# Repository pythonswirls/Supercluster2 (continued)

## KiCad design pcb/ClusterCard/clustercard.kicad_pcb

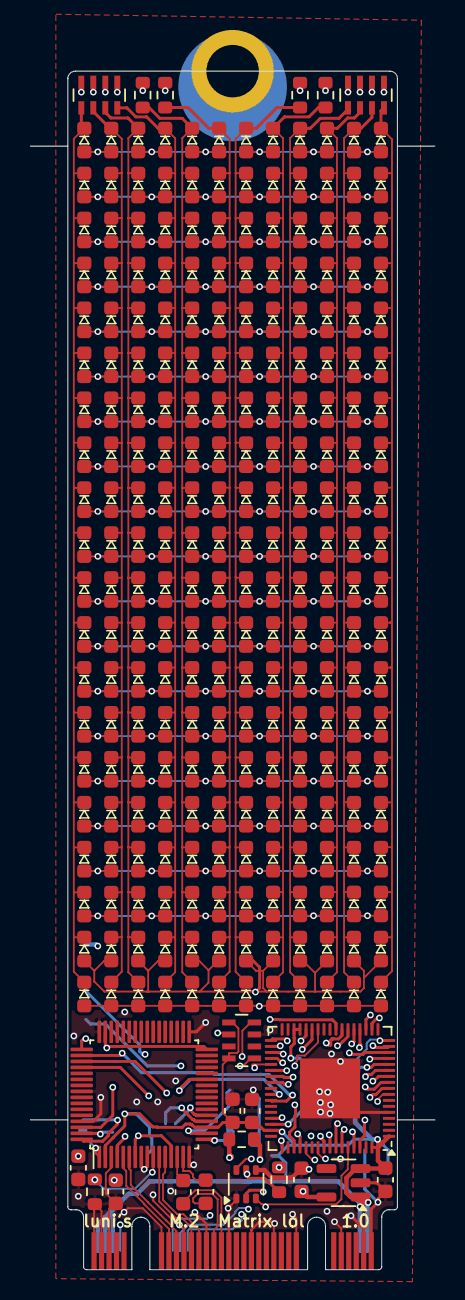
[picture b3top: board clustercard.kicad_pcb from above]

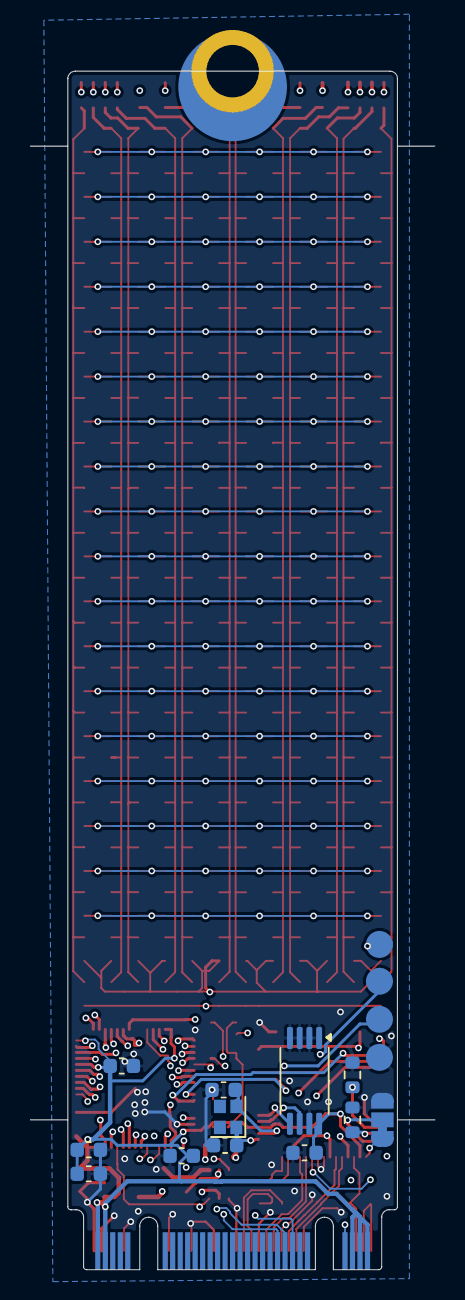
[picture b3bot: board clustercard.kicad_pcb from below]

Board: 4 copper layers, 27.0 x 80.0 mm, 276 parts (13 on the bottom side), 77 nets.

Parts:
C1, C2, C3, C10, C12, C15, C21, C22, C23, C24, C25: 100n; C_0603_1608Metric
C8, C11: 10u; C_0603_1608Metric
C16, C17: 27p; C_0603_1608Metric
D121, D122, D123, D124, D125, D126, D127, D128, D129, D130, D131, D132, D133, D134, D135, D136, D137, D138, D139, D140, D141, D142, D143, D144, D145, D146, D147, D148, D149, D150, D151, D152, D153, D154, D155, D156, D157, D158, D159, D160, D161, D162, D163, D164, D165, D166, D167, D168, D169, D170, D171, D172, D173, D174, D175, D176, D177, D178, D179, D180, D181, D182, D183, D184, D185, D186, D187, D188, D189, D190, D191, D192, D193, D194, D195, D196, D197, D198, D199, D200, D201, D202, D203, D204, D205, D206, D207, D208, D209, D210, D211, D212, D213, D214, D215, D216, D217, D218, D219, D220, D221, D222, D223, D224, D225, D226, D227, D228, D229, D230, D231, D232, D233, D234, D235, D236, D237, D238, D239, D240, D241, D242, D243, D244, D245, D246, D247, D248, D249, D250, D251, D252, D253, D254, D255, D256, D257, D258, D259, D260, D261, D262, D263, D264, D265, D266, D267, D268, D269, D270, D271, D272, D273, D274, D275, D276, D277, D278, D279, D280, D281, D282, D283, D284, D285, D286, D287, D288, D289, D290, D291, D292, D293, D294, D295, D296, D297, D298, D299, D300, D301, D302, D303, D304, D305, D306, D307, D308, D309, D310, D311, D312, D313, D314, D315, D316, D317, D318, D319, D320, D321, D322, D323, D324, D325, D326, D327, D328, D329, D330, D331, D332, D333, D334, D335, D336, D337, D338, D339, D340, D341, D342, D343, D344, D345, D346, D347, D348, D349, D350, D351, D352, D353, D354, D355, D356, D357, D358, D359, D360: LEDdiag0603; LED_0603
JP2: Jumper_3_Bridged12; SolderJumper-3_P1.3mm_Bridged12_RoundedPad1.0x1.5mm
Q1: UMH3N; SOT-363_SC-70-6
R8, R13, R14, R15, R16: 1k; R_0603_1608Metric
R9, R10, R11: 0; R_0603_1608Metric
R12: 12k; R_0603_1608Metric
RN5, RN6: 1k; R_Array_Concave_4x0603
RN8: 10k; R_Array_Concave_4x0603
TP1: TestPoint; Testpoint4
U1: CH382; LQFP-64_7x7mm_P0.4mm
U2: M.2-B+M-KEY-PCIe; M.2-B+M-KEY 2280
U4: M24C02-FDW; TSSOP-8_4.4x3mm_P0.65mm
U5: QFN-68-1EP_8x8mm_P0.4mm_EP4x4mm
U6: AP2112K-1.8; SOT-23-5
Y1: 22.1184MHz; Crystal_SMD_2016-4Pin_2.0x1.6mm

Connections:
1V8: C10.2, C11.2, R9.1, U1.4 (VCC18), U1.32 (VCC18), U1.47 (VCC18), U6.5 (VOUT)
1V8A: C12.2, R9.2, U1.7 (VCC18A), U1.13 (VCC18A)
/BOOT1: R8.2, U5.28 (PB2/BOOT1)
/CKSEL: JP2.2 (C), U1.64 (CKSEL)
/CLKREQ#: RN8.2 (R2.1), U2.P$52 (CLKREQ#)
/CLK_32k: U2.P$68 (SUSCLK(32kHz)), U5.58 (PB3)
/DTR: Q1.2 (B1), U1.52 (DTR0)
/PECK+: U1.5 (PECK+), U2.P$55 (REFCLK+)
/PECK-: U1.6 (PECK-), U2.P$53 (REFCLK-)
/PER+: U1.11 (PER+), U2.P$49 (PER0+)
/PER-: U1.12 (PER-), U2.P$47 (PER0-)
/PET+: C2.2, U1.15 (PET+)
/PET-: C1.2, U1.14 (PET-)
/RST#: JP2.1 (A), U1.1 (PERST#), U2.P$50 (PERST#)
/RST_CH32#: Q1.6 (C1), RN8.8 (R1.2), U5.8 (NRST)
/RTS: Q1.5 (B2), R8.1, U1.51 (RTS0)
/RX: U1.27 (RXD0), U5.44 (PA9)
/TX: U1.50 (TXD0), U5.45 (PA10)
/WAKE#: U2.P$54 (PEWAKE#), U5.56 (PC12)
BOOT0: Q1.3 (C2), RN8.5 (R4.2), U5.63 (BOOT0)
GND: C3.1, C8.1, C10.1, C11.1, C12.1, C15.1, C16.2, C17.2, C21.2, C22.2, C23.2, C24.2, C25.2, JP2.3 (B), Q1.1 (E1), Q1.4 (E2), R10.2, R11.2, R12.2, RN8.7 (R2.2), TP1.1, U1.3 (GND), U1.8 (GND), U1.9 (GND), U1.16 (GND), U1.33 (GND), U1.48 (GND), U1.56 (GND), U1.61 (GND), U2.P$1 (CONFIG3/GND), U2.P$3 (GND), U2.P$9 (GND), U2.P$21 (CONFIG_0/GND), U2.P$27 (GND), U2.P$33 (GND), U2.P$39 (GND), U2.P$45 (GND), U2.P$51 (GND), U2.P$57 (GND), U2.P$71 (GND), U2.P$73 (GND), U2.P$75 (CONFIG_2/GND), U4.1 (E0), U4.2 (E1), U4.3 (E2), U4.4 (VSS), U4.7 (~WC), U5.5 (VSSA), U5.49 (VSS_2), U5.69 (VSS), U6.2 (GND)
unnamed: D121.1 (K), D133.1 (K), D145.1 (K), D157.1 (K), D169.1 (K), D181.1 (K), D193.1 (K), D205.1 (K), D217.1 (K), D229.1 (K), D241.1 (K), D253.1 (K), D265.1 (K), D277.1 (K), D289.1 (K), D301.1 (K), D313.1 (K), D325.1 (K), D337.1 (K), D349.1 (K), RN5.4 (R4.1)
unnamed: D122.1 (K), D134.1 (K), D146.1 (K), D158.1 (K), D170.1 (K), D182.1 (K), D194.1 (K), D206.1 (K), D218.1 (K), D230.1 (K), D242.1 (K), D254.1 (K), D266.1 (K), D278.1 (K), D290.1 (K), D302.1 (K), D314.1 (K), D326.1 (K), D338.1 (K), D350.1 (K), RN5.3 (R3.1)
unnamed: D123.1 (K), D135.1 (K), D147.1 (K), D159.1 (K), D171.1 (K), D183.1 (K), D195.1 (K), D207.1 (K), D219.1 (K), D231.1 (K), D243.1 (K), D255.1 (K), D267.1 (K), D279.1 (K), D291.1 (K), D303.1 (K), D315.1 (K), D327.1 (K), D339.1 (K), D351.1 (K), RN5.2 (R2.1)
unnamed: D124.1 (K), D136.1 (K), D148.1 (K), D160.1 (K), D172.1 (K), D184.1 (K), D196.1 (K), D208.1 (K), D220.1 (K), D232.1 (K), D244.1 (K), D256.1 (K), D268.1 (K), D280.1 (K), D292.1 (K), D304.1 (K), D316.1 (K), D328.1 (K), D340.1 (K), D352.1 (K), RN5.1 (R1.1)
unnamed: D125.1 (K), D137.1 (K), D149.1 (K), D161.1 (K), D173.1 (K), D185.1 (K), D197.1 (K), D209.1 (K), D221.1 (K), D233.1 (K), D245.1 (K), D257.1 (K), D269.1 (K), D281.1 (K), D293.1 (K), D305.1 (K), D317.1 (K), D329.1 (K), D341.1 (K), D353.1 (K), R13.1
unnamed: D126.1 (K), D138.1 (K), D150.1 (K), D162.1 (K), D174.1 (K), D186.1 (K), D198.1 (K), D210.1 (K), D222.1 (K), D234.1 (K), D246.1 (K), D258.1 (K), D270.1 (K), D282.1 (K), D294.1 (K), D306.1 (K), D318.1 (K), D330.1 (K), D342.1 (K), D354.1 (K), R14.1
unnamed: D127.1 (K), D139.1 (K), D151.1 (K), D163.1 (K), D175.1 (K), D187.1 (K), D199.1 (K), D211.1 (K), D223.1 (K), D235.1 (K), D247.1 (K), D259.1 (K), D271.1 (K), D283.1 (K), D295.1 (K), D307.1 (K), D319.1 (K), D331.1 (K), D343.1 (K), D355.1 (K), R15.1
unnamed: D128.1 (K), D140.1 (K), D152.1 (K), D164.1 (K), D176.1 (K), D188.1 (K), D200.1 (K), D212.1 (K), D224.1 (K), D236.1 (K), D248.1 (K), D260.1 (K), D272.1 (K), D284.1 (K), D296.1 (K), D308.1 (K), D320.1 (K), D332.1 (K), D344.1 (K), D356.1 (K), R16.1
unnamed: D129.1 (K), D141.1 (K), D153.1 (K), D165.1 (K), D177.1 (K), D189.1 (K), D201.1 (K), D213.1 (K), D225.1 (K), D237.1 (K), D249.1 (K), D261.1 (K), D273.1 (K), D285.1 (K), D297.1 (K), D309.1 (K), D321.1 (K), D333.1 (K), D345.1 (K), D357.1 (K), RN6.4 (R4.1)
unnamed: D130.1 (K), D142.1 (K), D154.1 (K), D166.1 (K), D178.1 (K), D190.1 (K), D202.1 (K), D214.1 (K), D226.1 (K), D238.1 (K), D250.1 (K), D262.1 (K), D274.1 (K), D286.1 (K), D298.1 (K), D310.1 (K), D322.1 (K), D334.1 (K), D346.1 (K), D358.1 (K), RN6.3 (R3.1)
unnamed: D131.1 (K), D143.1 (K), D155.1 (K), D167.1 (K), D179.1 (K), D191.1 (K), D203.1 (K), D215.1 (K), D227.1 (K), D239.1 (K), D251.1 (K), D263.1 (K), D275.1 (K), D287.1 (K), D299.1 (K), D311.1 (K), D323.1 (K), D335.1 (K), D347.1 (K), D359.1 (K), RN6.2 (R2.1)
unnamed: D132.1 (K), D144.1 (K), D156.1 (K), D168.1 (K), D180.1 (K), D192.1 (K), D204.1 (K), D216.1 (K), D228.1 (K), D240.1 (K), D252.1 (K), D264.1 (K), D276.1 (K), D288.1 (K), D300.1 (K), D312.1 (K), D324.1 (K), D336.1 (K), D348.1 (K), D360.1 (K), RN6.1 (R1.1)
unnamed: R11.1, U1.62 (MDPRT#)
unnamed: R10.1, U1.63 (MDSEL)
unnamed: R12.1, U1.10 (RREF)
unnamed: U1.20 (SCL), U4.6 (SCL)
unnamed: U1.21 (SDA), U4.5 (SDA)
unnamed: C16.1, U1.18 (XI), Y1.2
unnamed: C17.1, U1.17 (XO), Y1.1
unnamed: C2.1, U2.P$43 (PET0+)
unnamed: C1.1, U2.P$41 (PET0-)
PA0: D121.2 (A), D122.2 (A), D123.2 (A), D124.2 (A), D125.2 (A), D126.2 (A), D127.2 (A), D128.2 (A), D129.2 (A), D130.2 (A), D131.2 (A), D132.2 (A), U5.14 (PA0/WKUP/ADC0)
PA1: D133.2 (A), D134.2 (A), D135.2 (A), D136.2 (A), D137.2 (A), D138.2 (A), D139.2 (A), D140.2 (A), D141.2 (A), D142.2 (A), D143.2 (A), D144.2 (A), U5.15 (PA1/ADC1)
PA2: D145.2 (A), D146.2 (A), D147.2 (A), D148.2 (A), D149.2 (A), D150.2 (A), D151.2 (A), D152.2 (A), D153.2 (A), D154.2 (A), D155.2 (A), D156.2 (A), U5.16 (PA2/ADC2)
PA3: D157.2 (A), D158.2 (A), D159.2 (A), D160.2 (A), D161.2 (A), D162.2 (A), D163.2 (A), D164.2 (A), D165.2 (A), D166.2 (A), D167.2 (A), D168.2 (A), U5.19 (PA3/ADC3)
PA4: D169.2 (A), D170.2 (A), D171.2 (A), D172.2 (A), D173.2 (A), D174.2 (A), D175.2 (A), D176.2 (A), D177.2 (A), D178.2 (A), D179.2 (A), D180.2 (A), U5.20 (PA4/ADC4)
PA5: D181.2 (A), D182.2 (A), D183.2 (A), D184.2 (A), D185.2 (A), D186.2 (A), D187.2 (A), D188.2 (A), D189.2 (A), D190.2 (A), D191.2 (A), D192.2 (A), U5.21 (PA5/ADC5)
PA6: D193.2 (A), D194.2 (A), D195.2 (A), D196.2 (A), D197.2 (A), D198.2 (A), D199.2 (A), D200.2 (A), D201.2 (A), D202.2 (A), D203.2 (A), D204.2 (A), U5.22 (PA6/ADC6)
PA7: D205.2 (A), D206.2 (A), D207.2 (A), D208.2 (A), D209.2 (A), D210.2 (A), D211.2 (A), D212.2 (A), D213.2 (A), D214.2 (A), D215.2 (A), D216.2 (A), U5.23 (PA7/ADC7)
PB4: D217.2 (A), D218.2 (A), D219.2 (A), D220.2 (A), D221.2 (A), D222.2 (A), D223.2 (A), D224.2 (A), D225.2 (A), D226.2 (A), D227.2 (A), D228.2 (A), U5.59 (PB4)
PB5: D229.2 (A), D230.2 (A), D231.2 (A), D232.2 (A), D233.2 (A), D234.2 (A), D235.2 (A), D236.2 (A), D237.2 (A), D238.2 (A), D239.2 (A), D240.2 (A), U5.60 (PB5)
PB6: D241.2 (A), D242.2 (A), D243.2 (A), D244.2 (A), D245.2 (A), D246.2 (A), D247.2 (A), D248.2 (A), D249.2 (A), D250.2 (A), D251.2 (A), D252.2 (A), U5.61 (PB6/USB2DM)
PB7: D253.2 (A), D254.2 (A), D255.2 (A), D256.2 (A), D257.2 (A), D258.2 (A), D259.2 (A), D260.2 (A), D261.2 (A), D262.2 (A), D263.2 (A), D264.2 (A), U5.62 (PB7/USB2DP)
PB8: D265.2 (A), D266.2 (A), D267.2 (A), D268.2 (A), D269.2 (A), D270.2 (A), D271.2 (A), D272.2 (A), D273.2 (A), D274.2 (A), D275.2 (A), D276.2 (A), U5.64 (PB8)
PB9: D277.2 (A), D278.2 (A), D279.2 (A), D280.2 (A), D281.2 (A), D282.2 (A), D283.2 (A), D284.2 (A), D285.2 (A), D286.2 (A), D287.2 (A), D288.2 (A), U5.65 (PB9)
PB10: D289.2 (A), D290.2 (A), D291.2 (A), D292.2 (A), D293.2 (A), D294.2 (A), D295.2 (A), D296.2 (A), D297.2 (A), D298.2 (A), D299.2 (A), D300.2 (A), U5.29 (PB10)
PB11: D301.2 (A), D302.2 (A), D303.2 (A), D304.2 (A), D305.2 (A), D306.2 (A), D307.2 (A), D308.2 (A), D309.2 (A), D310.2 (A), D311.2 (A), D312.2 (A), U5.30 (PB11)
PB12: D313.2 (A), D314.2 (A), D315.2 (A), D316.2 (A), D317.2 (A), D318.2 (A), D319.2 (A), D320.2 (A), D321.2 (A), D322.2 (A), D323.2 (A), D324.2 (A), U5.35 (PB12)
PB13: D325.2 (A), D326.2 (A), D327.2 (A), D328.2 (A), D329.2 (A), D330.2 (A), D331.2 (A), D332.2 (A), D333.2 (A), D334.2 (A), D335.2 (A), D336.2 (A), U5.36 (PB13)
PB14: D337.2 (A), D338.2 (A), D339.2 (A), D340.2 (A), D341.2 (A), D342.2 (A), D343.2 (A), D344.2 (A), D345.2 (A), D346.2 (A), D347.2 (A), D348.2 (A), U5.37 (PB14)
PB15: D349.2 (A), D350.2 (A), D351.2 (A), D352.2 (A), D353.2 (A), D354.2 (A), D355.2 (A), D356.2 (A), D357.2 (A), D358.2 (A), D359.2 (A), D360.2 (A), U5.38 (PB15)
PC0: RN5.5 (R4.2), U5.9 (PC0/ADC10)
PC1: RN5.6 (R3.2), U5.10 (PC1/ADC11)
PC2: RN5.7 (R2.2), U5.11 (PC2/ADC12)
PC3: RN5.8 (R1.2), U5.12 (PC3/ADC13)
PC4: R13.2, U5.24 (PC4/ADC14)
PC5: R14.2, U5.25 (PC5/ADC15)
PC6: R15.2, U5.39 (PC6/RXP)
PC7: R16.2, U5.40 (PC7/RXN)
PC8: RN6.5 (R4.2), U5.41 (PC8/TXP)
PC9: RN6.6 (R3.2), U5.42 (PC9/TXN)
PC10: RN6.7 (R2.2), U5.54 (PC10)
PC11: RN6.8 (R1.2), U5.55 (PC11)
SWDCLK: TP1.2, U5.52 (PA14/SWCLK)
SWDIO: TP1.3, U5.48 (PA13/SWDIO)
VCC: C3.2, C8.2, C15.2, C21.1, C22.1, C23.1, C24.1, C25.1, RN8.1 (R1.1), RN8.4 (R4.1), TP1.4, U1.2 (VCC33), U1.19 (VCC33), U1.49 (VCC33), U2.P$2 (3V3), U2.P$4 (3V3), U2.P$70 (3V3), U2.P$72 (3V3), U2.P$74 (3V3), U4.8 (VCC), U5.1 (VBAT), U5.13 (VDDA), U5.17 (VIO_4), U5.31 (VIO_1), U5.32 (VDD_1), U5.50 (VINTA), U5.67 (VIO_3), U5.68 (VDD_3), U6.1 (VIN), U6.3 (EN)

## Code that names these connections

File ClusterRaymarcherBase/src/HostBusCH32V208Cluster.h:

#pragma once
#include "HostBus.h"
#include <stdint.h>
#include <ch32v20x.h>

class HostBusCH32V208: public HostBus
{
	public:
	HostBusCH32V208()
		:HostBus()
	{
	}

	virtual bool initIo()
	{
		//initialize GPIOs
		RCC_APB2PeriphClockCmd(RCC_APB2Periph_GPIOA, ENABLE);
		RCC_APB2PeriphClockCmd(RCC_APB2Periph_GPIOB, ENABLE);
		RCC_APB2PeriphClockCmd(RCC_APB2Periph_GPIOC, ENABLE);
	
		//16 CMD lines for MCUs
		GPIOC->OUTDR = 0xffff;
		GPIOC->CFGLR = 0x33333333; //set PC0-PC7 to push pull output, 50MHz
		GPIOC->CFGHR = 0x44433333; //set PC8-PC15 to push pull output, 50MHz
		GPIOB->CFGLR = 0x33333333;

		uint32_t cfg = 0;
		for(int i = 0; i < 8; i++)
			cfg |= (0b0100 /*open drain*/ | 0b11 /*50MHz output*/) << (4 * i);
		GPIOA->BSHR = 0xff;    //for open drain need to leave high for others to speak
		GPIOA->CFGLR = cfg;
		
		cfg = 0;
		for(int i = 0; i < 8; i++)
			if(i == 1 || i == 7) //avoid D1 and D7 to have swio still active
				cfg |= (0b0100 /*floating*/ | 0b00 /*input*/) << (4 * i);
			else
				cfg |= (0b0100 /*open drain*/ | 0b11 /*30MHz output*/) << (4 * i);
		GPIOB->BSHR = 0x7d00;
		GPIOB->BCR  = 0x8200;
		GPIOB->CFGHR = cfg;
		return true;
	}

	virtual void enableReceive()
	{
	}

	virtual void enableTransmit()
	{
	}

	virtual void disableReceive()
	{
	}

	virtual void disableTransmit()
	{
	}

	virtual void setACK() 
	{
		GPIOB->BCR = 0b0001000000000000; 	//set PB12 low, ready to receive or transmit
	}

	virtual void resetACK()
	{
		GPIOB->BSHR = 0b0001000000000000; 	//set PB12 high, reset ready to receive or transmit
	}

	virtual bool getACK()
	{
		return (GPIOB->INDR & 0b0001000000000000) == 0;	 //get PB12
	}

	virtual void setFULL()
	{
		GPIOB->BCR = 0b0010000000000000; //set PB13 low, ready to receive or transmit
	}

	virtual void resetFULL()
	{
		GPIOB->BSHR = 0b0010000000000000; //set PB13 low, ready to receive or transmit
	}

	virtual bool getFULL()
	{
		return (GPIOB->INDR & 0b0010000000000000) == 0; //get PB13
	}

	virtual void setEOT() 
	{
		GPIOB->BCR = 0b0100000000000000; //set PB14 low, end of transmission
	}

	virtual void resetEOT()
	{
		GPIOB->BSHR = 0b0100000000000000; 
	}
	
	virtual bool getEOT()
	{
		return (GPIOB->INDR & 0b0100000000000000) == 0; 	//get PB14
	}
	
	virtual void setType(RequestType type)
	{
		//TODO one write
		GPIOB->BCR = 0b0000110000000000; //set PB10 and PB11 low, request type
		GPIOB->BSHR = (uint32_t)type << 10; //set PB10 and PB11 to type
	}

	virtual void resetType()
	{
		GPIOB->BSHR = 0b0000110000000000; //set PB10 and PB11 high, reset request type
	}

	virtual RequestType getType()
	{
		return (RequestType)((GPIOD->INDR >> 10) & 0b11); //get PB10 and PB11, request type
	}

	virtual void setData(uint8_t data)
	{
		GPIOA->BCR = 0b11111111; 
		GPIOA->BSHR = (uint32_t)data;
	}

	virtual uint8_t getData()
	{
		return (uint8_t)(GPIOA->INDR & 0xff);
	}

	virtual void resetData() 
	{
		GPIOA->BSHR = 0b11111111; //set PB0-PB7 high, reset data
	};

	virtual void setCMD(uint16_t lines)
	{
		GPIOC->BCR = lines;
		GPIOB->BCR = lines >> 13;
	}

	virtual void resetCMD(uint16_t lines)
	{
		GPIOC->BSHR = lines;
		GPIOB->BSHR = lines >> 13;
	}

	virtual uint16_t getCMD()
	{
		return (GPIOC->INDR & 0xffff)^0xffff; 
	}

	virtual bool getCLK()
	{
		return (GPIOB->INDR & 0b0000000100000000) == 0; //get PB8
	}

	virtual void setCLK()
	{
		GPIOB->BCR = 0b0000000100000000; //set PB8 low, reset clock
	}

	virtual void resetCLK()
	{
		GPIOB->BSHR = 0b0000000100000000; //set PB8 high, reset clock
	}

	virtual void processReceivedData()
	{
		//not needed
	}
};

HostBusCH32V208 bus;

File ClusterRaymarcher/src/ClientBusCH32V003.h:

#pragma once
#include "ClientBus.h"
#include <stdint.h>
#include <ch32v00x.h>
#include <core_riscv.h>
#include "utils.h"

void  busInterrupt(void) __attribute__((interrupt("WCH-Interrupt-fast")));

class ClientBusCH32V003: public ClientBus
{
	public:
	ClientBusCH32V003()
		:ClientBus()
	{
	}

	virtual bool initIo()
	{
		//initialize GPIOs
		RCC_APB2PeriphClockCmd(RCC_APB2Periph_GPIOA, ENABLE);
		RCC_APB2PeriphClockCmd(RCC_APB2Periph_GPIOC, ENABLE);
		RCC_APB2PeriphClockCmd(RCC_APB2Periph_GPIOD, ENABLE);
	
		/*uint32_t cfg = 0;
		for(int i = 0; i < 8; i++)
			cfg |= (0b0100 | 0b11 ) << (4 * i); // open drain output
		GPIOC->OUTDR = 0b11111111;    //for open drain need to leave high for others to speak
		GPIOC->CFGLR = cfg;
		cfg = 0;
		for(int i = 0; i < 8; i++)
			if(i == 1 || i == 7) //avoid D1 and D7 to have swio still active
				cfg |= (0b0100 | 0b00 ) << (4 * i); //floating input
			else
				cfg |= (0b0100| 0b11 ) << (4 * i); //open drain output
		*/
		GPIOC->OUTDR = 0b11111111;
		GPIOC->CFGLR = 0x77777777; //open drain (except d1 and d7		
		//GPIOC->CFGLR = 0x44444444; //floating

		GPIOD->OUTDR = 0b01111101;
		//GPIOD->CFGLR = cfg;
		//GPIOD->CFGLR = 0x44444444; //floating
		GPIOD->CFGLR = 0x47777747; //open drain (except d1 and d7

		//GPIOA->CFGLR = (GPIOA->CFGLR & 0b000011110000) |  ((0b0100 /*floating*/ | 0b00 /*input*/) << (4 * 2));
		GPIOA->CFGLR = (GPIOA->CFGLR & 0x0f0) | 0x400;
	
		//initialize interrupts
		RCC_APB2PeriphClockCmd(RCC_APB2Periph_AFIO, ENABLE);

		//GPIO A2 interrupt
		AFIO->EXTICR = (AFIO->EXTICR & ~AFIO_EXTICR1_EXTI2) | AFIO_EXTICR1_EXTI2_PA;	//line 2 on PA2
		EXTI->INTENR |= EXTI_INTENR_MR2; // Enable EXT7 on line 2
		//EXTI->RTENR |= EXTI_RTENR_TR2;  // Rising edge trigger
		EXTI->FTENR |= EXTI_FTENR_TR2;  // Falling edge trigger	

		//GPIO D0 interrupt prepare
		AFIO->EXTICR = (AFIO->EXTICR & ~AFIO_EXTICR1_EXTI0) | AFIO_EXTICR1_EXTI0_PD;	//line 0 on PD0
		//EXTI->INTENR |= EXTI_INTENR_MR0; // Enable EXT7 on line 0
		EXTI->RTENR |= EXTI_RTENR_TR0;  // Rising edge trigger
		EXTI->FTENR |= EXTI_FTENR_TR0;  // Falling edge trigger	
	
		SetVTFIRQ((uint32_t)busInterrupt, EXTI7_0_IRQn, 0, ENABLE);
		NVIC_EnableIRQ(EXTI7_0_IRQn);
	
		return true;
	}

	virtual void enableReceive()
	{
		EXTI->INTENR |= EXTI_INTENR_MR0; // Enable EXT7 on line 0
	}

	virtual void enableTransmit()
	{
		//GPIOC->OUTDR = 0b11111111;
		//GPIOC->CFGLR = 0x77777777; //open drain (except d1 and d7)
		EXTI->INTENR |= EXTI_INTENR_MR0; // Enable EXT7 on line 0
	}

	virtual void disableReceive()
	{
		EXTI->INTENR &= ~EXTI_INTENR_MR0; 	// Disable EXT7 on line 0
		GPIOD->BSHR = 0b01111101;			//release open drain lines, avoid D1 and D7 here to have swio still active
	}

	virtual void disableTransmit()
	{
		EXTI->INTENR &= ~EXTI_INTENR_MR0; 	// Disable EXT7 on line 0
		GPIOC->BSHR = 0b11111111; 			//release open drain lines
		//GPIOC->CFGLR = 0x44444444; 			//floating
		GPIOD->BSHR = 0b01111101;			//release open drain lines, avoid D1 and D7 here to have swio still active
	}

	virtual void setACK() 
	{
		GPIOD->BCR = 0b00010000; //set PD4 low, ready to receive or transmit
	}

	virtual void resetACK()
	{
		GPIOD->BSHR = 0b00010000; //set PD4 high, not ready
	}

	virtual bool getACK()
	{
		return (GPIOD->INDR & 0b00010000) == 0;
	}

	virtual void setFULL()
	{
		GPIOD->BCR = 0b00100000; //set PD5 low, ready to receive or transmit
	}

	virtual void resetFULL()
	{
		GPIOD->BSHR = 0b00100000; //set PD5 low, ready to receive or transmit
	}

	virtual bool getFULL()
	{
		return (GPIOD->INDR & 0b00100000) == 0; //get PD5
	}

	virtual void setEOT() 
	{
		GPIOD->BCR = 0b01000000; //set PD6 low, end of transmission
	}

	virtual void resetEOT()
	{
		GPIOD->BSHR = 0b01000000; //set PD6 high, not end of transmission
	}
	
	virtual bool getEOT()
	{
		return (GPIOD->INDR & 0b01000000) == 0; //get PD6
	}
	
	virtual void setType(RequestType type)
	{
		GPIOD->BCR = 0b00001100; //set PD2 and PD3 low, request type
		GPIOD->BSHR = (uint32_t)type << 2; //set PD2 and PD3 high, request type
	}

	virtual RequestType getType()
	{
		return (RequestType)((GPIOD->INDR & 0b00001100) >> 2); //get PD2 and PD3
	}

	virtual void setData(uint8_t data)
	{
		GPIOC->OUTDR = (uint32_t)data; //set PC0-PC7 data
	}

	virtual uint8_t getData()
	{
		return (uint8_t)(GPIOC->INDR & 0xff); //get PC0-PC7 data
	}

	virtual void resetData() 
	{
		GPIOC->OUTDR = 0b11111111; //set PC0-PC7 high, reset data
	};

	virtual void processReceivedData()
	{
		//copy packet trigger processing
	}

	virtual bool getCLK()
	{
		return (GPIOD->INDR & 0b00000001) == 0; //get PD0
	}

	virtual uint16_t getCMD()
	{
		return ((GPIOA->INDR >> 2) & 1) == 0; //get PA 2
	}

	virtual void debug(uint8_t data) 
	{
		led(data? 1 : 0);
	};
};

ClientBusCH32V003 bus;
void __attribute__((interrupt("WCH-Interrupt-fast"))) busInterrupt(void)
{
    if(EXTI->INTFR & EXTI_Line2)
	{
		bus.handleRequest();
		EXTI->INTFR = EXTI_Line2;
	}
	if(EXTI->INTFR & EXTI_Line0)
	{
		if(!bus.getCLK()) //PD0 is high
			bus.handleDataClockHigh();
		else
			bus.handleDataClockLow();
		EXTI->INTFR = EXTI_Line0;
	}
}

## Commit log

2025-05-14 3 versions. 1: fpu, 2:fpu with many slow tasks. 3:fixed point with rsqrt
2025-05-14 unshift too slow. reverse priority https://github.com/bitluni/Supercluster2/issues/1
2025-05-14 scene data now in scene object. can be serialized and sent to workers
2025-05-14 parallel workers version
2025-05-14 lower res sorry :-)
2025-05-14 max thread count for your system
2025-05-15 oops some debugging slipped in
2025-05-15 cloned CDC project
2025-05-15 c++ conversion
2025-05-15 new try
2025-05-15 compiling
2025-05-15 ignore
2025-05-15 argh
2025-05-15 does not work
2025-05-16 working CDC with ch32x208 and pio
2025-05-16 compiling raymarcher
2025-05-16 vibed webserial example to send receive packets. fixed a few cdc renderer bugs and sending binary counter to webserial
2025-05-16 working raymarcher on MCU over serial
2025-05-21 ch32v003 cluster project added
2025-05-21 fixed noneos-sdk missing clock setting to 48MHz internal
2025-05-21 added include for weird systems
2025-05-21 irst raymarcher version for ch32v003 including bus communication
2025-05-21 source
2025-06-02 refactoring cluster bus
2025-06-03 last changes before bus redesign
2025-06-04 new bus.. not worky yet
2025-06-05 some bugs fixed. some left
2025-06-05 first working version with new bus
2025-06-06 broadcast working
2025-06-06 ping works now
2025-06-06 severe errors fixed. tests for rendering a pixel
2025-06-07 concurrent rendering. communication might bug out, though
2025-06-11 trying to fix all the bugs, without luck. this project kills me
2025-06-11 latest stream changes
2025-06-12 reworking host to only act as realy. tools need to be adjusted now
2025-06-13 host function updated
2025-06-13 broken state
2025-06-13 fixed hse hsi bug
2025-06-13 new timer methods
2025-06-14 lot of fixes. blink was blocking communication. converted to timeout
2025-06-14 LED seems to affect evereything. deactivated on ping
2025-06-14 raymarcher updated to new bus. working with 16 MCUs
2025-06-14 extra fixes
2025-07-05 release
2025-07-05 PCBs added
